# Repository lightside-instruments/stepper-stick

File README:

stepper-stick is an open hardware board for driving 2-phase stepper motors
published by Lightside Instruments AS.

The initial release stepper-stick-1.0 includes schematic and PCB
design files for KiCAD.

The project is published byC Lightside Instruments AS
under TAPR Open Hardware License. Read the LICENSE file
for details.

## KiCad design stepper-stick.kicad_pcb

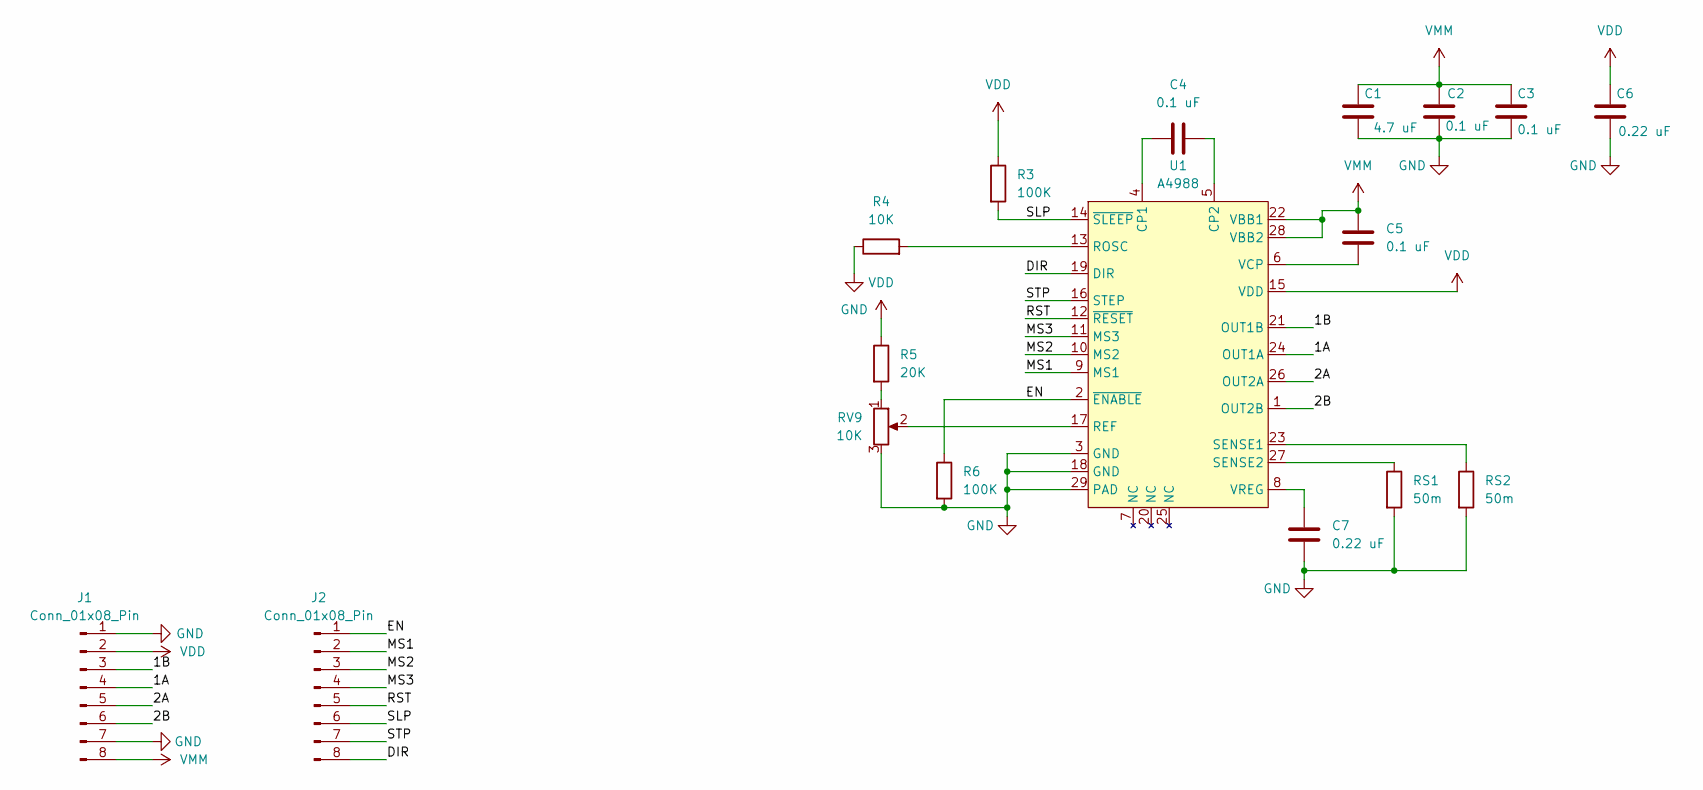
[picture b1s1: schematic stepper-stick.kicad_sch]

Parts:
C1: 4.7 uF; C_1206_3216Metric
C2, C3, C4, C5: 0.1 uF; C_0402_1005Metric
C6, C7: 0.22 uF; C_0402_1005Metric
J1, J2: Conn_01x08_Pin; PinHeader_1x08_P2.54mm_Vertical
R3, R6: 100K; R_0402_1005Metric
R4: 10K; R_0402_1005Metric
R5: 20K; R_0402_1005Metric
RS1, RS2: 50m; R_0603_1608Metric
RV9: 10K; Potentiometer_Bourns_TC33X_Vertical
U1: A4988; QFN-28-1EP_5x5mm_P0.5mm_EP3.35x3.35mm_ThermalVias; MPN A4988SETTR-T; LCSC Part C38437

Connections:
/1A: J1.4, U1.24 (OUT1A)
/1B: J1.3, U1.21 (OUT1B)
/2A: J1.5, U1.26 (OUT2A)
/2B: J1.6, U1.1 (OUT2B)
/DIR: J2.8, U1.19 (DIR)
/EN: J2.1, R6.1, U1.2 (~ENABLE)
/MS1: J2.2, U1.9 (MS1)
/MS2: J2.3, U1.10 (MS2)
/MS3: J2.4, U1.11 (MS3)
/RST: J2.5, U1.12 (~RESET)
/SLP: J2.6, R3.2, U1.14 (~SLEEP)
/STP: J2.7, U1.16 (STEP)
GND: C1.2, C2.2, C3.2, C6.2, C7.2, J1.1, J1.7, R4.1, R6.2, RS1.2, RS2.2, RV9.3, U1.3 (GND), U1.18 (GND), U1.29 (PAD)
unnamed: R5.2, RV9.1
unnamed: C4.2, U1.4 (CP1)
unnamed: C4.1, U1.5 (CP2)
unnamed: RV9.2, U1.17 (REF)
unnamed: R4.2, U1.13 (ROSC)
unnamed: RS2.1, U1.23 (SENSE1)
unnamed: RS1.1, U1.27 (SENSE2)
unnamed: C5.2, U1.6 (VCP)
unnamed: C7.1, U1.8 (VREG)
VDD: C6.1, J1.2, R3.1, R5.1, U1.15 (VDD)
VMM: C1.1, C2.1, C3.1, C5.1, J1.8, U1.22 (VBB1), U1.28 (VBB2)

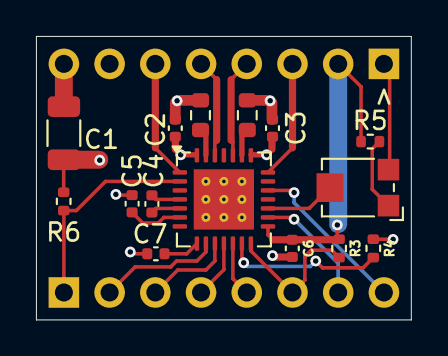
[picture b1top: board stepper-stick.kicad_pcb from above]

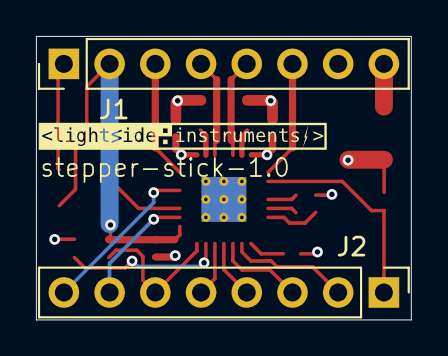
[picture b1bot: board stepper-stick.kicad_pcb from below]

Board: 4 copper layers, 20.8 x 15.7 mm, 18 parts (3 on the bottom side), 24 nets.

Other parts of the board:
svg2mod: G***; lsi-logo-16mm
